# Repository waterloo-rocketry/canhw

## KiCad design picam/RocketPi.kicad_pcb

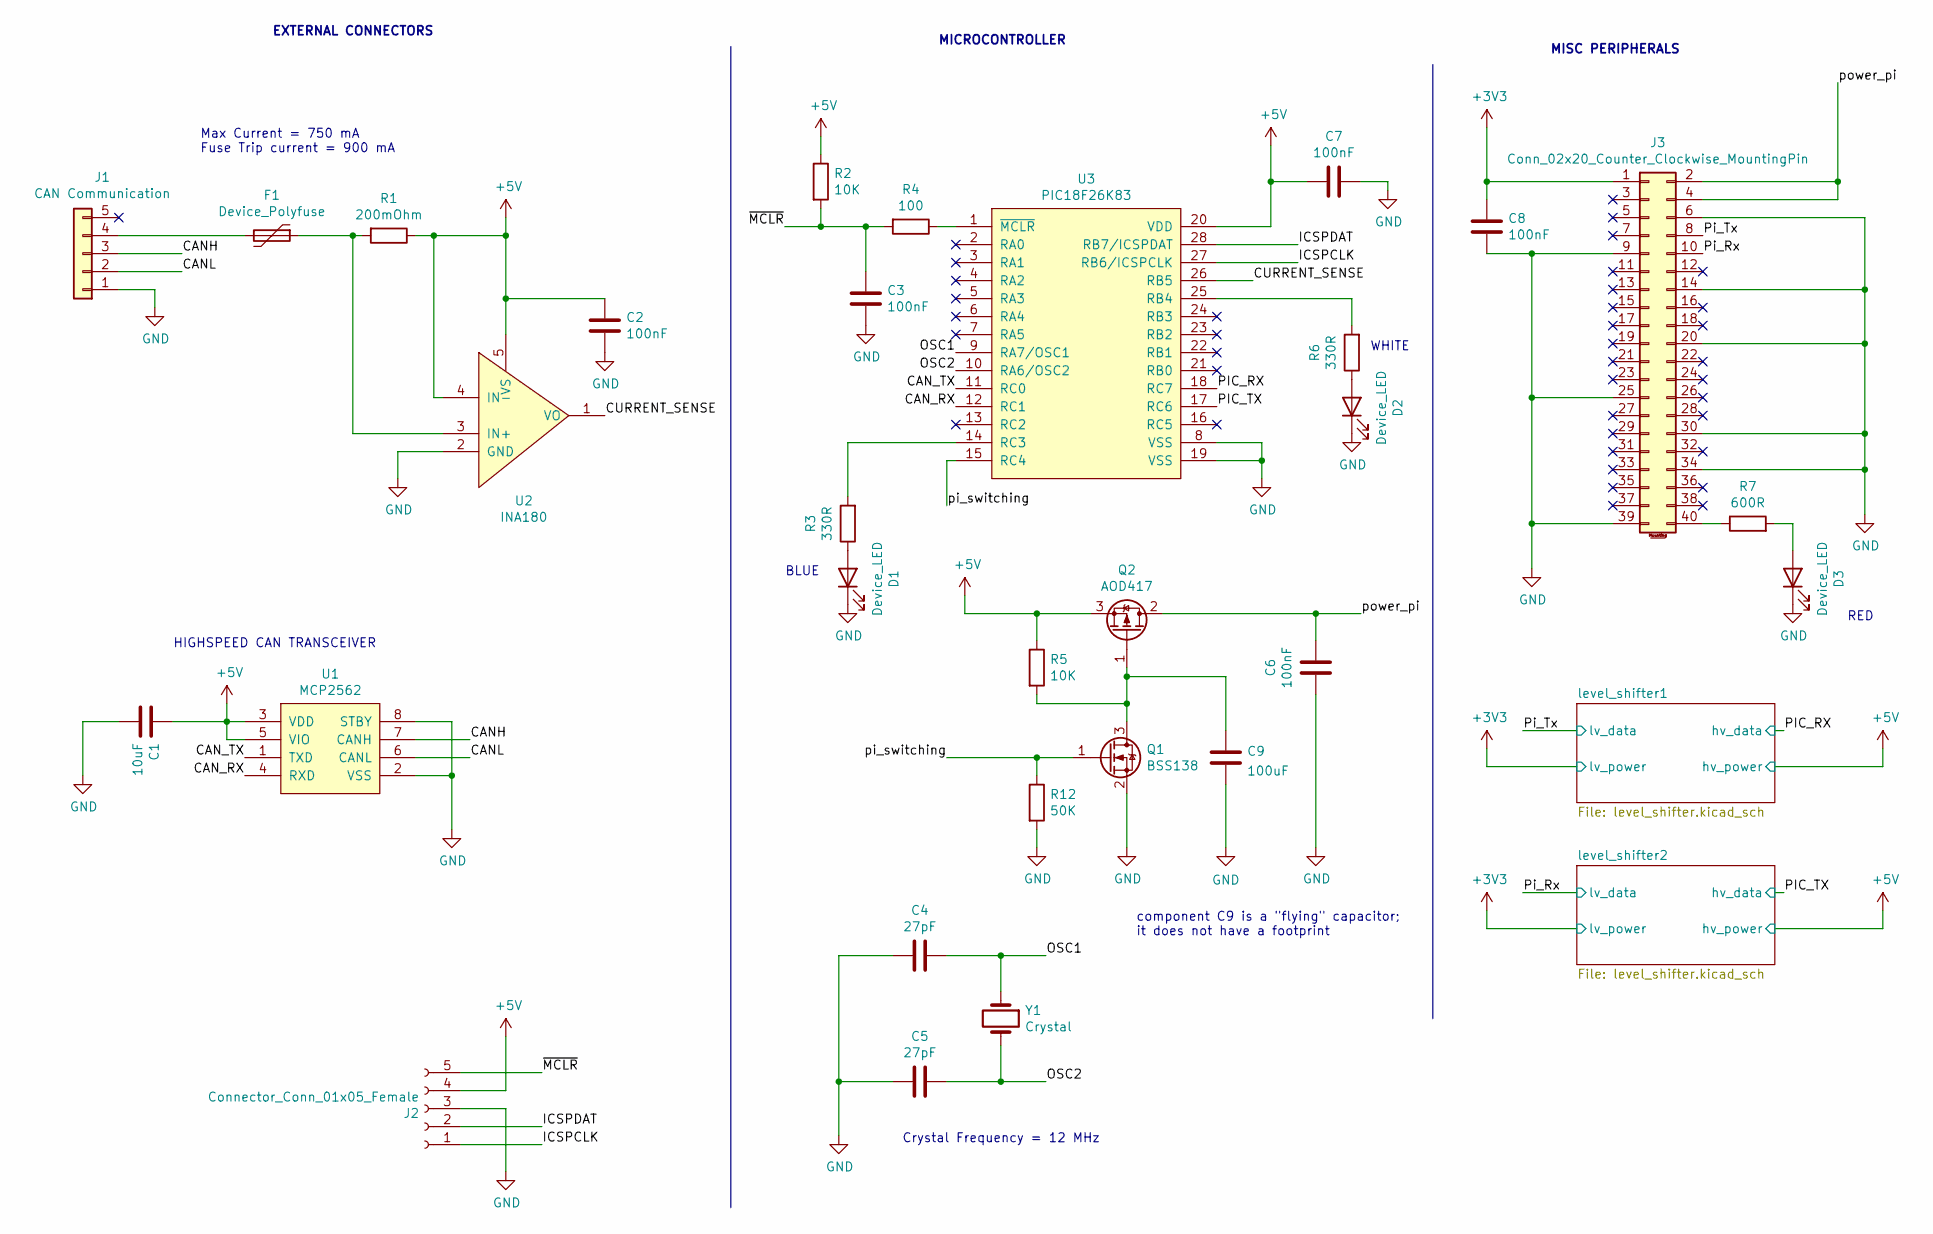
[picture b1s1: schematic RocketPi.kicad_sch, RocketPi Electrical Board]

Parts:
C1: 10uF; C_0805_2012Metric_Pad1.15x1.40mm_HandSolder
C2, C3, C6, C7, C8: 100nF; C_0805_2012Metric_Pad1.15x1.40mm_HandSolder
C4, C5: 27pF; C_0805_2012Metric_Pad1.15x1.40mm_HandSolder
C9: 100uF
D1, D2, D3: Device_LED; LED_0805_2012Metric_Pad1.15x1.40mm_HandSolder
F1: Device_Polyfuse; Fuse_0805_2012Metric_Pad1.15x1.40mm_HandSolder
J1: CAN Communication; connector_Harwin_M80-5000642
J2: Connector_Conn_01x05_Female; PinHeader_5x2.54_SMD_90deg_952-3198-1-ND
J3: Conn_02x20_Counter_Clockwise_MountingPin; PinHeader_2x20_P2.54mm_Vertical
Q1: BSS138; SOT-23
Q2: AOD417; TO-252-2
R1: 200mOhm; R_0805_2012Metric_Pad1.15x1.40mm_HandSolder
R2, R5: 10K; R_0805_2012Metric_Pad1.15x1.40mm_HandSolder
R3, R6: 330R; R_0805_2012Metric_Pad1.15x1.40mm_HandSolder
R4: 100; R_0805_2012Metric_Pad1.15x1.40mm_HandSolder
R7: 600R; R_0805_2012Metric_Pad1.15x1.40mm_HandSolder
R12: 50K; R_0805_2012Metric_Pad1.15x1.40mm_HandSolder
U1: MCP2562; SOIC-8_3.9x4.9mm_P1.27mm
U2: INA180; SOT-23-5_HandSoldering
U3: PIC18F26K83; SOIC-28W_7.5x17.9mm_P1.27mm
Y1: Crystal; Crystal_HC49-U_Vertical

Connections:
+3V3: C8.1, J3.1; also elsewhere on the board
+5V: C1.1, C2.1, C7.2, J2.4, Q2.3 (S), R1.1, R2.1, R5.1, U1.3 (VDD), U1.5 (VIO), U2.4 (IN-), U2.5 (VS), U3.20 (VDD); also elsewhere on the board
/CANH: J1.3, U1.7 (CANH)
/CANL: J1.2, U1.6 (CANL)
/CAN_RX: U1.4 (RXD), U3.12 (RC1)
/CAN_TX: U1.1 (TXD), U3.11 (RC0)
/CURRENT_SENSE: U2.1 (VO), U3.26 (RB5)
/ICSPCLK: J2.1, U3.27 (RB6/ICSPCLK)
/ICSPDAT: J2.2, U3.28 (RB7/ICSPDAT)
/OSC1: C4.1, U3.9 (RA7/OSC1), Y1.1
/OSC2: C5.1, U3.10 (RA6/OSC2), Y1.2
/PIC_RX: U3.18 (RC7); also elsewhere on the board
/PIC_TX: U3.17 (RC6); also elsewhere on the board
/Pi_Rx: J3.10; also elsewhere on the board
/Pi_Tx: J3.8; also elsewhere on the board
/pi_switching: Q1.1 (G), R12.1, U3.15 (RC4)
/power_pi: C6.1, J3.2, J3.4, Q2.2 (D)
/~MCLR: C3.1, J2.5, R2.2, R4.2
GND: C1.2, C2.2, C3.2, C4.2, C5.2, C6.2, C7.1, C8.2, C9.2, D1.1 (K), D2.1 (K), D3.1 (K), J1.1, J2.3, J3.6, J3.9, J3.14, J3.20, J3.25, J3.30, J3.34, J3.39, Q1.2 (S), R12.2, U1.2 (VSS), U1.8 (STBY), U2.2 (GND), U3.8 (VSS), U3.19 (VSS)
unnamed: D1.2 (A), R3.1
unnamed: D2.2 (A), R6.1
unnamed: D3.2 (A), R7.2
unnamed: F1.1, R1.2, U2.3 (IN+)
unnamed: F1.2, J1.4
unnamed: J3.40, R7.1
unnamed: C9.1, Q1.3 (D), Q2.1 (G), R5.2
unnamed: R3.2, U3.14 (RC3)
unnamed: R4.1, U3.1 (~MCLR)
unnamed: R6.2, U3.25 (RB4)

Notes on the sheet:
component C9 is a "flying" capacitor; it does not have a footprint
BLUE
WHITE
Max Current = 750 mA Fuse Trip current = 900 mA
MISC PERIPHERALS
MICROCONTROLLER
RED
HIGHSPEED CAN TRANSCEIVER
EXTERNAL CONNECTORS
Crystal Frequency = 12 MHz

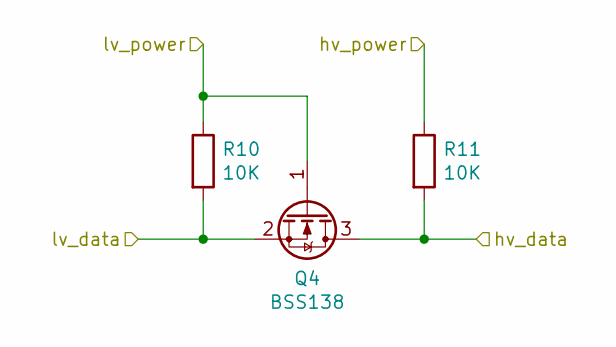
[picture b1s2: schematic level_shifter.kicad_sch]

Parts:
Q4: BSS138; SOT-23
R10, R11: 10K; R_0805_2012Metric_Pad1.15x1.40mm_HandSolder

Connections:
+3V3: Q4.1 (G), R10.1; also elsewhere on the board
+5V: R11.1; also elsewhere on the board
/PIC_TX: Q4.3 (D), R11.2; also elsewhere on the board
/Pi_Rx: Q4.2 (S), R10.2; also elsewhere on the board

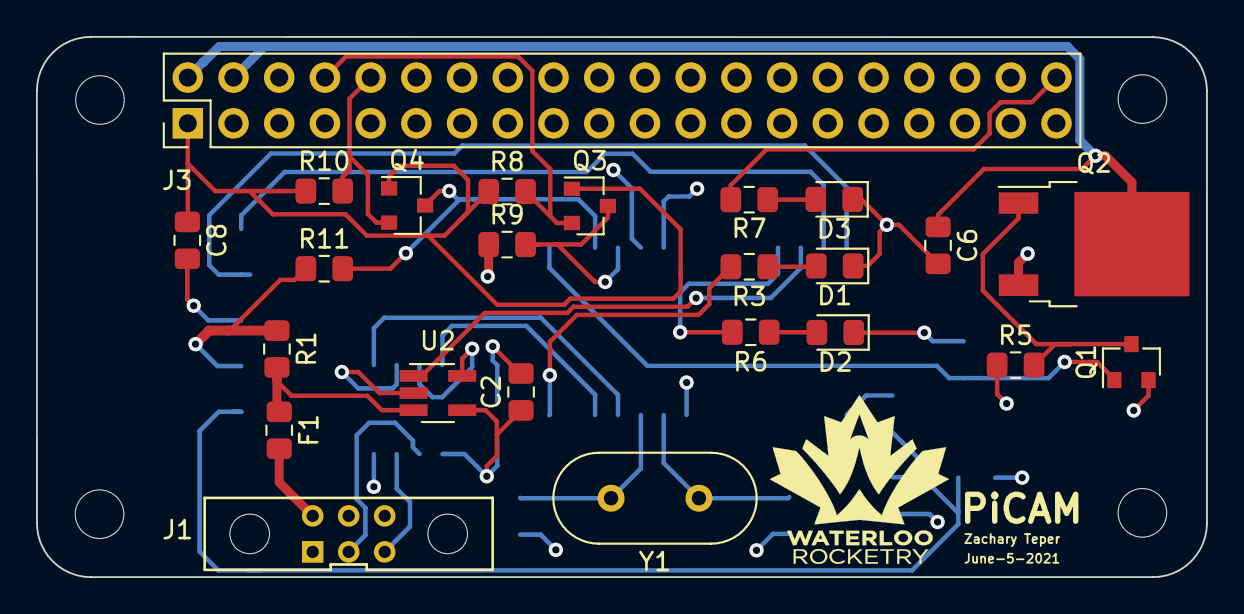
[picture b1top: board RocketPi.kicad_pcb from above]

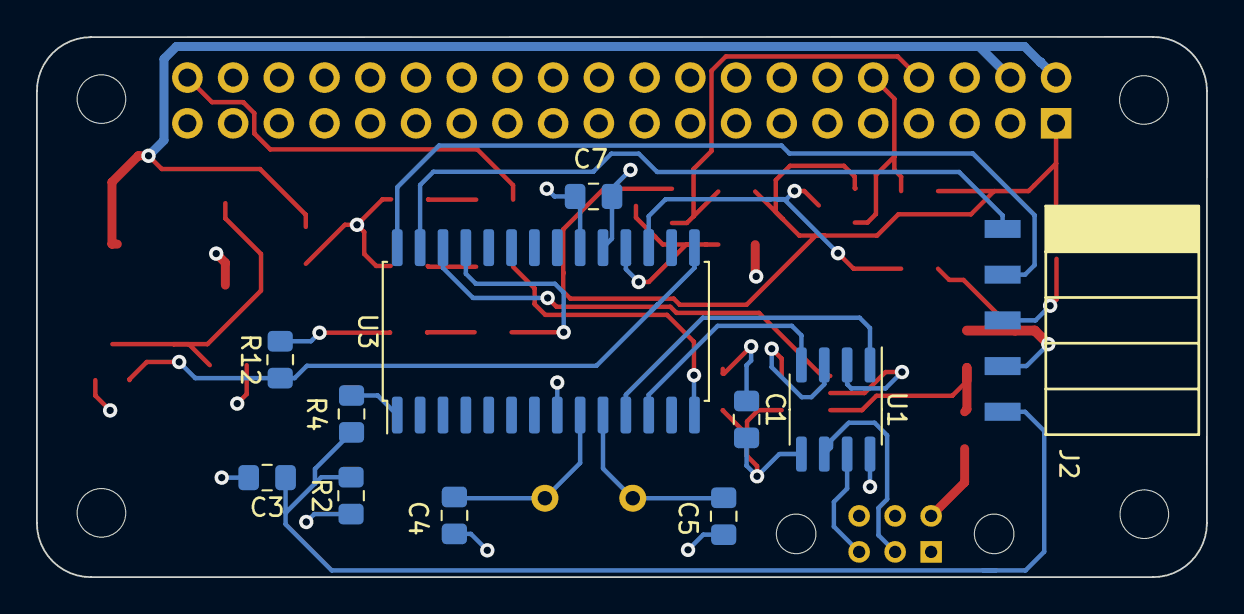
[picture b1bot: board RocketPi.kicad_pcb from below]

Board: 4 copper layers, 65.0 x 30.0 mm, 39 parts (11 on the bottom side), 29 nets.

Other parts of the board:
M1, M2, M3, M4: MountingHole_2.7mm
Q3: BSS138; SOT-23
R8, R9: 10K; R_0805_2012Metric_Pad1.15x1.40mm_HandSolder

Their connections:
+3V3: Q3.1, R8.1; also elsewhere on the board
+5V: R9.1; also elsewhere on the board
/PIC_RX: Q3.3, R9.2; also elsewhere on the board
/Pi_Tx: Q3.2, R8.2; also elsewhere on the board

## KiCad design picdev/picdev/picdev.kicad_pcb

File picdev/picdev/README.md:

This is a development board meant to be used for writing firmware for the CAN bus project while the main rocket boards are still in the hardware design phase. The board contains a PIC18F26K83 (which will be used on most subsystem boards inside the rocket) and a PIC16F1455 (which is used on the USB debug board). The PIC16F is connected to an external CAN module, allowing the two PICs to communicate with each other over CAN. 

The board is nicknamed "Keto" because it was borne out of a dislike of breadboards.

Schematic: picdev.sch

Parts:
C1, C2: 10uF; CP_Radial_D5.0mm_P2.50mm
F1: Fuse_Small; Fuse_1206_3216Metric_Pad1.24x1.80mm_HandSolder
J1: Power Conn; Pin_Header_Straight_1x02_Pitch2.54mm
J4: CAN Breakout; Pin_Header_Straight_1x02_Pitch2.54mm
JP1, JP2: Jumper_NC_Small; Pin_Header_Straight_1x02_Pitch2.54mm
R1: 120R; R_0805_HandSoldering
TP1, TP2: TestPoint; TestPoint_THTPad_D2.0mm_Drill1.0mm
U1: R-78E5.0-0.5; SIP3_11.6x8.5mm

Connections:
+5V: C2.1, U1.3; also elsewhere on the board
/PIC16F1455/CANH: J4.2, JP1.1; also elsewhere on the board
/PIC16F1455/CANL: J4.1, JP2.1; also elsewhere on the board
/PIC18F26K83/CANH: JP1.2, R1.1, TP1.1; also elsewhere on the board
/PIC18F26K83/CANL: JP2.2, R1.2, TP2.1; also elsewhere on the board
GND: C1.2, C2.2, J1.1, U1.2; also elsewhere on the board
unnamed: C1.1, F1.2, U1.1
unnamed: F1.1, J1.2

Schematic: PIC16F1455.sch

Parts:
C3, C5, C6: 0.1uF; C_0805_HandSoldering
C4: 10uF; CP_Radial_D5.0mm_P2.50mm
D1, D2: LED; LED_1206_3216Metric
J2: Programming Header; Pin_Header_Straight_1x05_Pitch2.54mm
J5: USB_B; USB_B_Horizontal
R2, R3: 10K; R_0805_HandSoldering
R4, R5: 330R; R_0805_HandSoldering
R12: 0; R_0805_HandSoldering
TP3, TP4: TestPoint; TestPoint_THTPad_D2.0mm_Drill1.0mm
U2: MCP2562; DIP-8_W7.62mm
U3: PIC16F1455; DIP-14_W7.62mm
U4: MCP2515; DIP-18_W7.62mm

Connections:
+5V: C4.1, C5.1, C6.1, D1.2, D2.2, J2.4, R2.1, R3.1, R12.1, U2.3 (VDD), U2.5 (VIO), U3.1 (VDD), U4.17 (~RESET), U4.18 (VDD); also elsewhere on the board
/PIC16F1455/CANH: U2.7 (CANH); also elsewhere on the board
/PIC16F1455/CANL: U2.6 (CANL); also elsewhere on the board
/PIC16F1455/CAN_INT: R3.2, U3.2 (RA5), U4.12 (~INT)
/PIC16F1455/CLKOUT: U3.3 (RA4), U4.8 (OSC1)
/PIC16F1455/CS: U3.7 (RC3), U4.16 (~CS)
/PIC16F1455/ICSPCLK: J2.1, U3.9 (RC1/ICSPCLK), U4.15 (SO)
/PIC16F1455/ICSPDAT: J2.2, U3.10 (RC0/ICSPDAT), U4.13 (SCK)
/PIC16F1455/MOSI: U3.8 (RC2), U4.14 (SI)
/PIC16F1455/USB_D+: J5.3 (D+), U3.13 (RA0/D+)
/PIC16F1455/USB_D-: J5.2 (D-), U3.12 (RA1/D-)
/PIC16F1455/~MCLR: J2.5, R2.2, U3.4 (RA3/~MCLR)
GND: C3.2, C4.2, C5.2, C6.2, J2.3, J5.4 (GND), J5.5 (Shield), U2.2 (VSS), U2.8 (STBY), U3.14 (VSS), U4.9 (VSS); also elsewhere on the board
unnamed: C3.1, U3.11 (VUSB3V3)
unnamed: D1.1, R4.1
unnamed: D2.1, R5.1
unnamed: J5.1 (VBUS), R12.2
unnamed: R4.2, U3.6 (RC4)
unnamed: R5.2, U3.5 (RC5)
unnamed: TP3.1, U2.1 (TXD), U4.1 (TXCAN)
unnamed: TP4.1, U2.4 (RXD), U4.2 (RXCAN)

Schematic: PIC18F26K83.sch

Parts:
C7: 0.1uF; C_0805_HandSoldering
C8: 10uF; CP_Radial_D5.0mm_P2.50mm
C9, C10: 26pF; C_0805_HandSoldering
D3, D4, D5, D6, D7: LED; LED_1206_3216Metric
J3: Programming Header; Pin_Header_Straight_1x05_Pitch2.54mm
J6: Conn_01x04_Female; Pin_Header_Straight_1x04_Pitch2.54mm
R6: 1OK; R_0805_HandSoldering
R7, R8, R9, R10, R11: 330R; R_0805_HandSoldering
TP5, TP6: TestPoint; TestPoint_THTPad_D2.0mm_Drill1.0mm
U5: MCP2562; DIP-8_W7.62mm
U6: PIC18F26K83; DIP-28_W7.62mm
Y1: Crystal; Crystal_HC49-4H_Vertical

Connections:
+5V: C7.2, C8.1, D3.2, D4.2, D5.2, D6.2, D7.2, J3.4, R6.1, U5.3 (VDD), U5.5 (VIO), U6.20; also elsewhere on the board
/PIC18F26K83/CANH: U5.7 (CANH); also elsewhere on the board
/PIC18F26K83/CANL: U5.6 (CANL); also elsewhere on the board
/PIC18F26K83/CAN_RX: TP6.1, U5.4 (RXD), U6.12
/PIC18F26K83/CAN_TX: TP5.1, U5.1 (TXD), U6.11
/PIC18F26K83/ICSPCLK: J3.1, U6.27
/PIC18F26K83/ICSPDAT: J3.2, U6.28
/PIC18F26K83/OSC1: C9.1, U6.9, Y1.1
/PIC18F26K83/OSC2: C10.1, U6.10, Y1.2
/PIC18F26K83/~MCLR: J3.5, R6.2, U6.1
GND: C7.1, C8.2, C9.2, C10.2, J3.3, U5.2 (VSS), U5.8 (STBY), U6.8, U6.19; also elsewhere on the board
unnamed: D3.1, R7.1
unnamed: D4.1, R8.1
unnamed: D5.1, R9.1
unnamed: D6.1, R10.1
unnamed: D7.1, R11.1
unnamed: J6.1, U6.2
unnamed: J6.2, U6.3
unnamed: J6.3, U6.4
unnamed: J6.4, U6.5
unnamed: R7.2, U6.25
unnamed: R8.2, U6.24
unnamed: R9.2, U6.23
unnamed: R10.2, U6.22
unnamed: R11.2, U6.21

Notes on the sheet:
completely unecessary

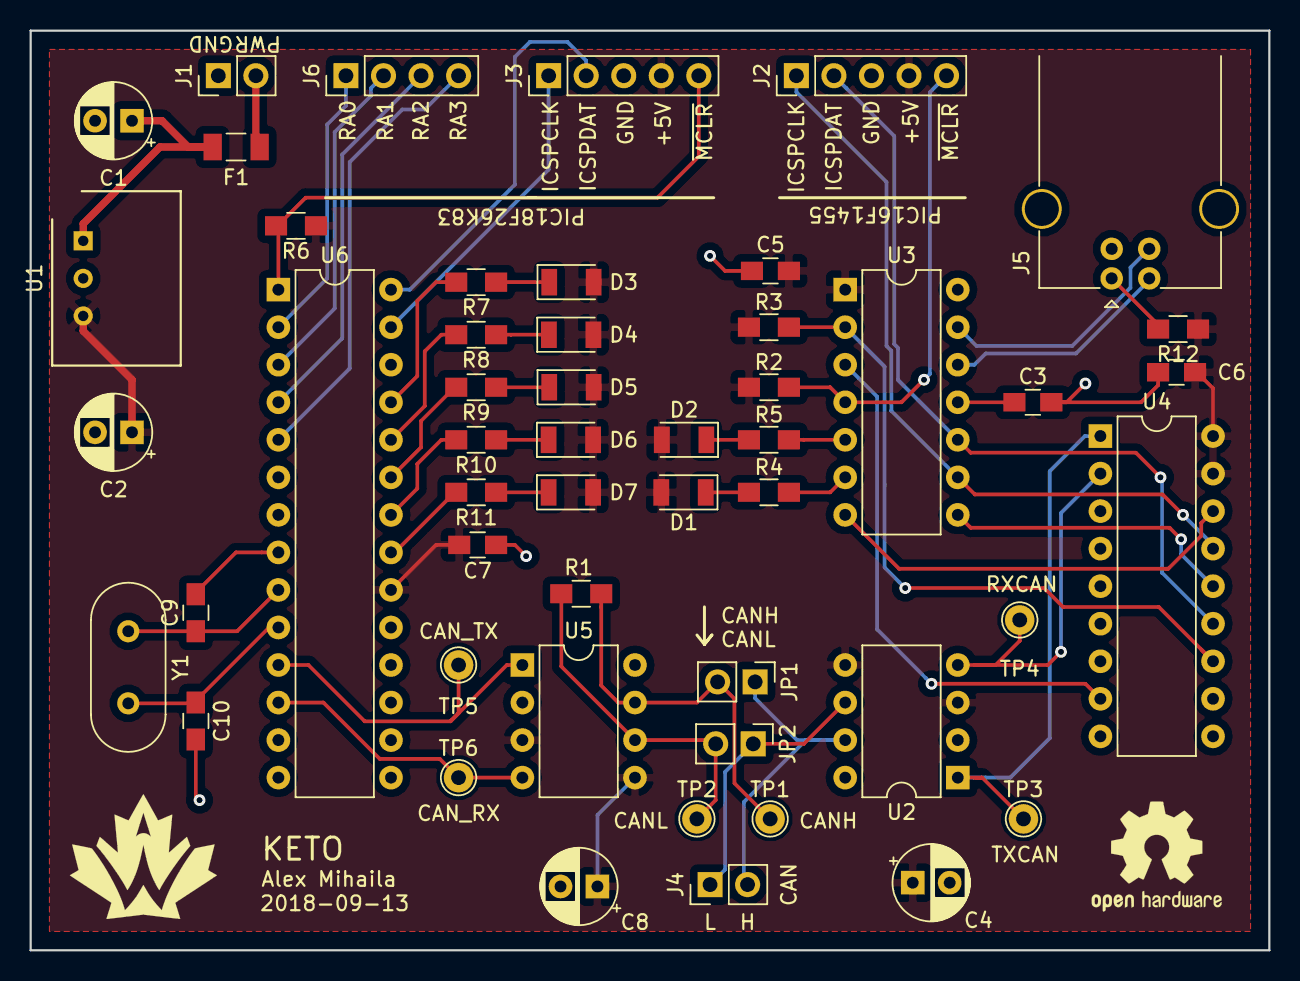
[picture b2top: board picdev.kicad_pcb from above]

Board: 2 copper layers, 83.8 x 62.2 mm, 51 parts (0 on the bottom side), 46 nets.

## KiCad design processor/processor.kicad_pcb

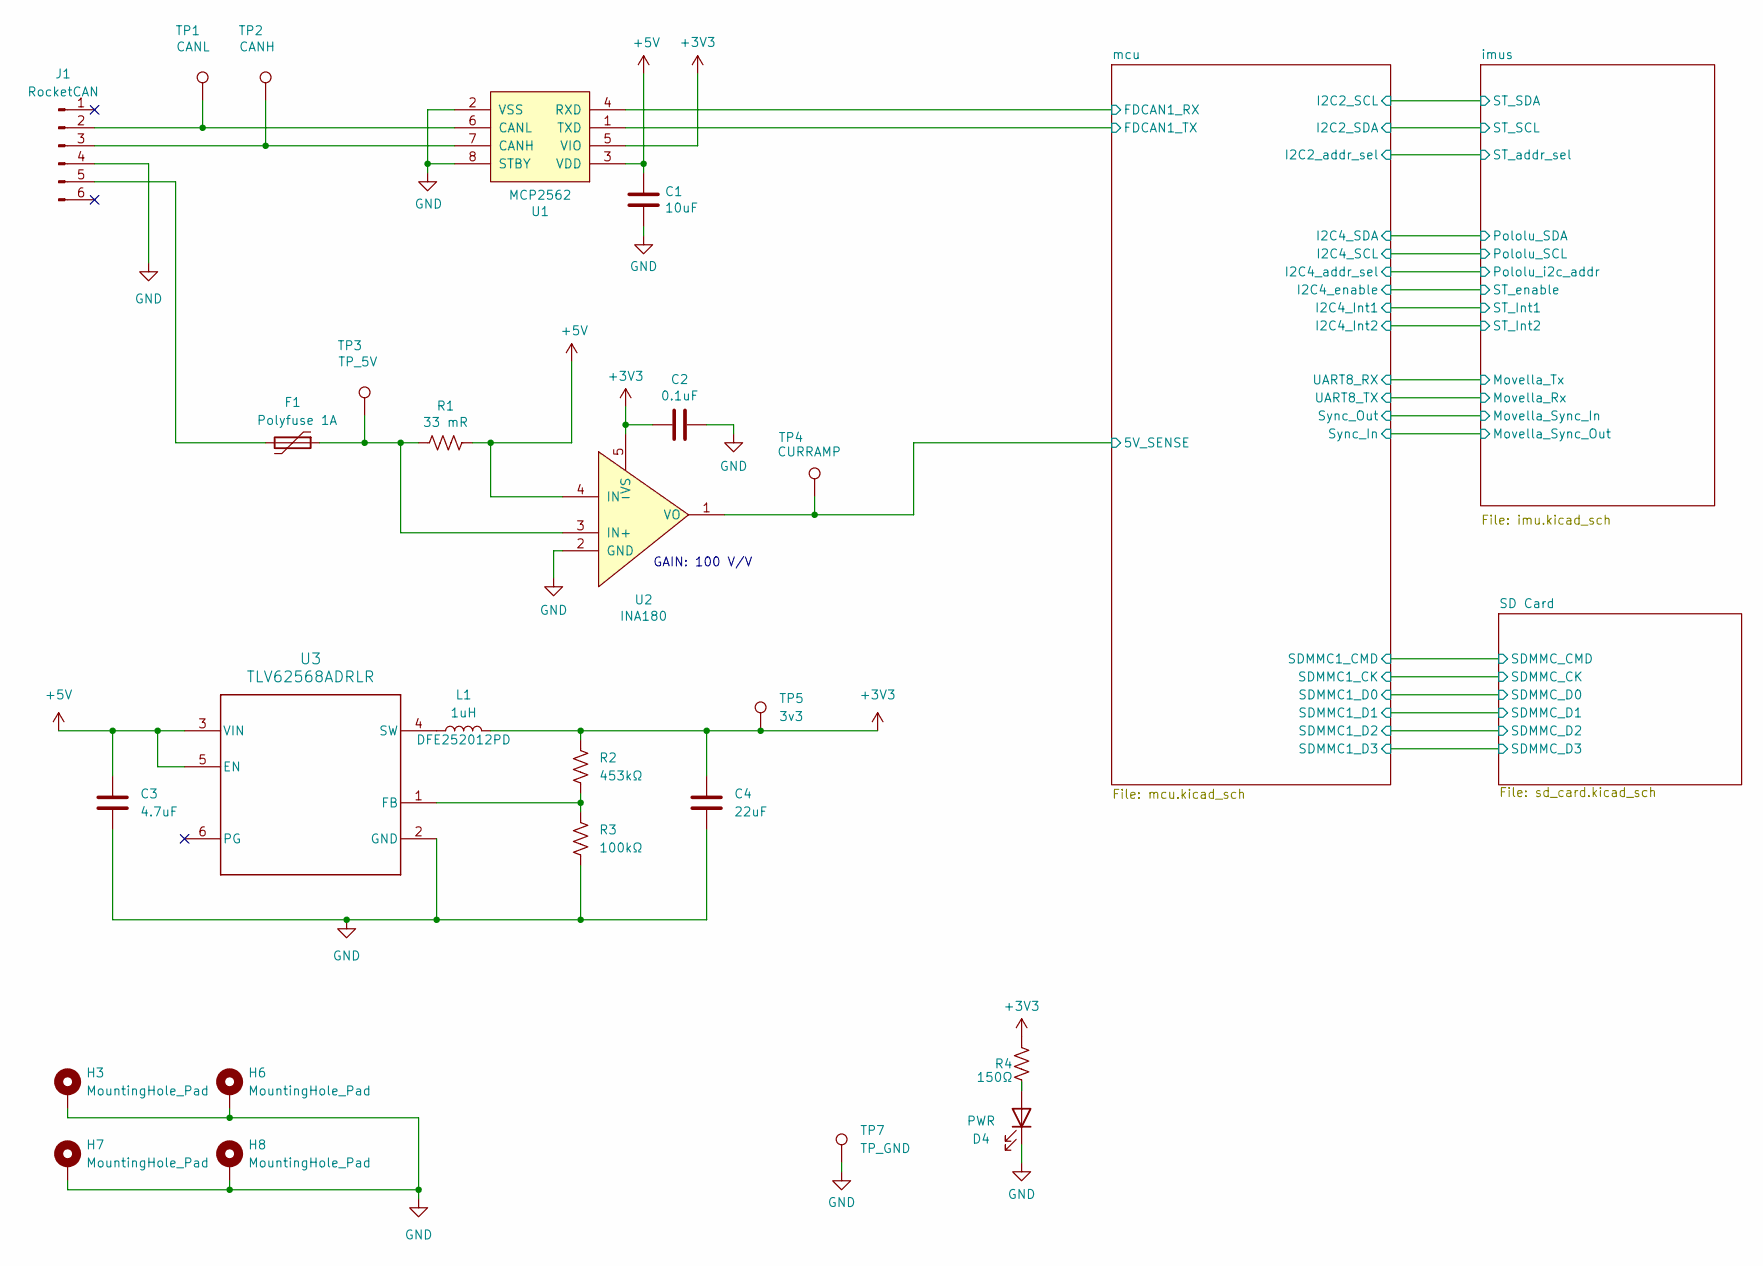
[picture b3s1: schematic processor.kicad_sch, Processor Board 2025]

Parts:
C1: 10uF; C_0805_2012Metric_Pad1.18x1.45mm_HandSolder; LCSC Part # C15850
C2: 0.1uF; C_0805_2012Metric_Pad1.18x1.45mm_HandSolder; LCSC Part # C49678
C3: 4.7uF; C_0805_2012Metric_Pad1.18x1.45mm_HandSolder; LCSC Part # C1779
C4: 22uF; C_0805_2012Metric_Pad1.18x1.45mm_HandSolder; LCSC Part # C45783
D4: PWR; LED_1206_3216Metric_Pad1.42x1.75mm_HandSolder; LCSC Part # C434441
F1: Polyfuse 1A; Fuse_1206_3216Metric_Pad1.42x1.75mm_HandSolder; LCSC Part # C20800
H3, H6, H7, H8: MountingHole_Pad; MountingHole_3.2mm_M3_DIN965_Pad
J1: RocketCAN; connector_Harwin_G125–MG10605M4P
L1: 1uH; IND_DFE252012PD-1R0M=P2_MUR; Part Number DFE252012PD; LCSC Part # C2917900
R1: 33 mR; R_1206_3216Metric_Pad1.30x1.75mm_HandSolder; LCSC Part # C912764
R2: 453kΩ; R_0805_2012Metric_Pad1.20x1.40mm_HandSolder; LCSC Part # C101739
R3: 100kΩ; R_0805_2012Metric_Pad1.20x1.40mm_HandSolder; LCSC Part # C149504
R4: 150Ω; R_0805_2012Metric_Pad1.20x1.40mm_HandSolder; LCSC Part # C17471
TP1: CANL; TestPoint_Pad_1.5x1.5mm
TP2: CANH; TestPoint_Pad_1.5x1.5mm
TP3: TP_5V; TestPoint_Keystone_5000-5004_Miniature
TP4: CURRAMP; TestPoint_Pad_1.5x1.5mm
TP5: 3v3; TestPoint_Keystone_5000-5004_Miniature
TP7: TP_GND; TestPoint_Keystone_5000-5004_Miniature
U1: MCP2562; SOIC-8_3.9x4.9mm_P1.27mm; LCSC Part # C191417
U2: INA180; SOT-23-5_HandSoldering; LCSC Part # C2059240
U3: TLV62568ADRLR; DRL0006A; LCSC Part # C398372

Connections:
+3V3: C2.2, C4.1, L1.2, R2.1, R4.1, TP5.1, U1.5 (VIO), U2.5 (VS); also elsewhere on the board
+5V: C1.1, C3.1, R1.1, U1.3 (VDD), U2.4 (IN-), U3.3 (VIN), U3.5 (EN); also elsewhere on the board
/mcu/5V_SENSE: TP4.1, U2.1 (VO); also elsewhere on the board
/mcu/FDCAN1_RX: U1.4 (RXD); also elsewhere on the board
/mcu/FDCAN1_TX: U1.1 (TXD); also elsewhere on the board
GND: C1.2, C2.1, C3.2, C4.2, D4.1 (K), H3.1, J1.4, R3.2, TP7.1, U1.2 (VSS), U1.8 (STBY), U2.2 (GND), U3.2 (GND); also elsewhere on the board
unnamed: D4.2 (A), R4.2
unnamed: J1.2, TP1.1, U1.6 (CANL)
unnamed: J1.3, TP2.1, U1.7 (CANH)
unnamed: F1.2, J1.5
unnamed: F1.1, R1.2, TP3.1, U2.3 (IN+)
unnamed: R2.2, R3.1, U3.1 (FB)
unnamed: L1.1, U3.4 (SW)

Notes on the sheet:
GAIN: 100 V/V

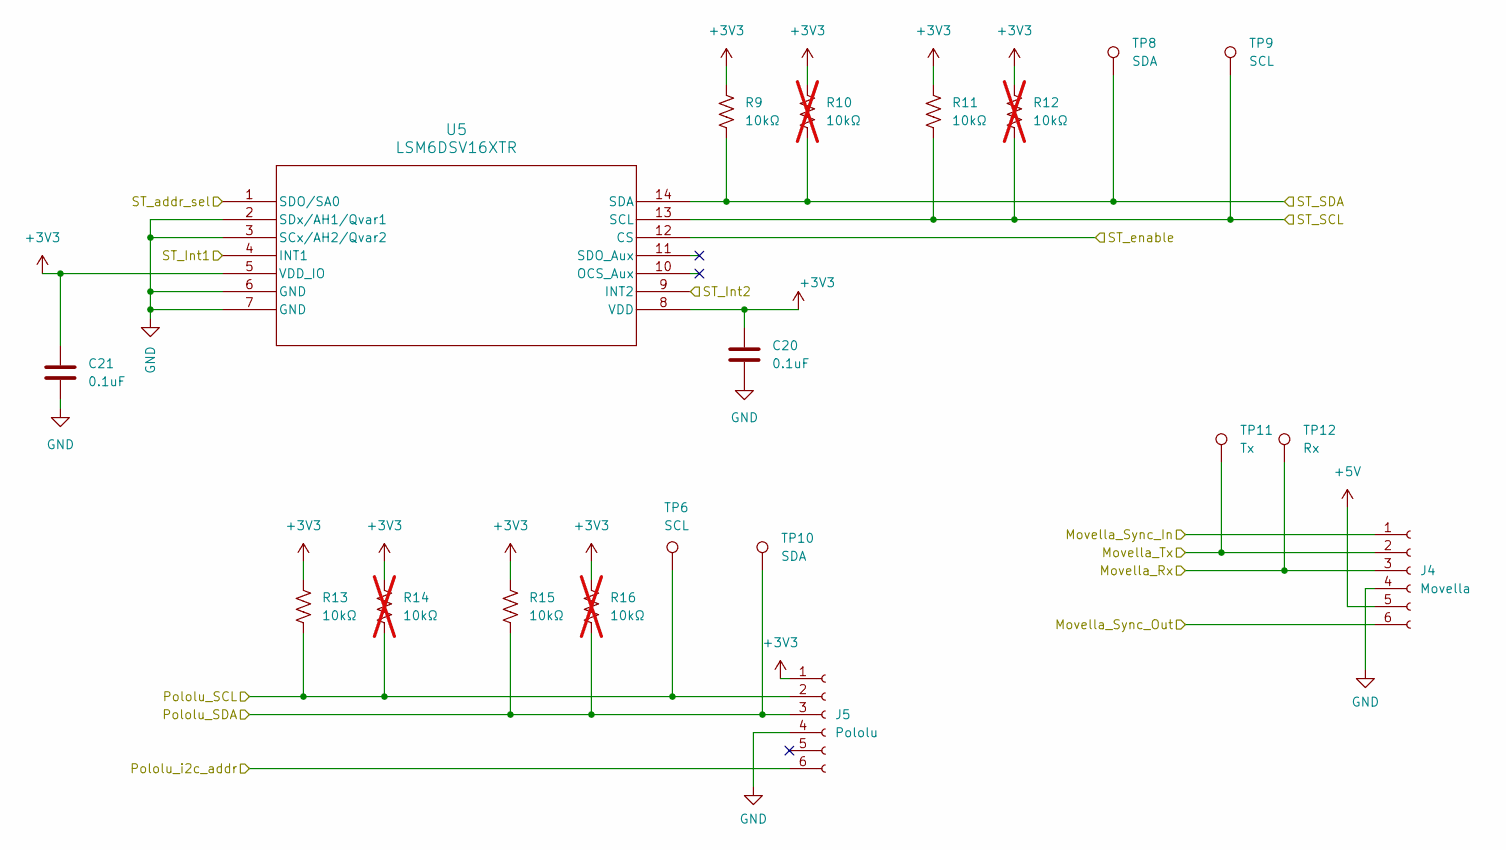
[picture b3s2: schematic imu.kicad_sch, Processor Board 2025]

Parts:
C20, C21: 0.1uF; C_0805_2012Metric_Pad1.18x1.45mm_HandSolder; LCSC Part # C49678
J4: Movella; connector_Harwin_G125–MG10605M4P
J5: Pololu; connector_Harwin_G125–MG10605M4P
R9, R11, R13, R15: 10kΩ; R_0805_2012Metric_Pad1.20x1.40mm_HandSolder; LCSC Part # C17414
R10, R12, R14, R16: 10kΩ; R_0805_2012Metric_Pad1.20x1.40mm_HandSolder; LCSC Part # C17414; not fitted
TP6: SCL; TestPoint_Keystone_5000-5004_Miniature
TP8: SDA; TestPoint_Pad_D1.5mm
TP9: SCL; TestPoint_Pad_D1.5mm
TP10: SDA; TestPoint_Keystone_5000-5004_Miniature
TP11: Tx; TestPoint_Keystone_5000-5004_Miniature
TP12: Rx; TestPoint_Keystone_5000-5004_Miniature
U5: LSM6DSV16XTR; LGA-14L_2p5X3p0X0p86_STM; LCSC Part # C5267406

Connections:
+3V3: C20.1, C21.1, J5.1, R9.1, R10.1, R11.1, R12.1, R13.1, R14.1, R15.1, R16.1, U5.5 (VDD_IO), U5.8 (VDD); also elsewhere on the board
+5V: J4.5; also elsewhere on the board
/imus/Movella_Rx: J4.3, TP12.1; also elsewhere on the board
/imus/Movella_Sync_In: J4.1; also elsewhere on the board
/imus/Movella_Sync_Out: J4.6; also elsewhere on the board
/imus/Movella_Tx: J4.2, TP11.1; also elsewhere on the board
/imus/Pololu_SCL: J5.2, R13.2, R14.2, TP6.1; also elsewhere on the board
/imus/Pololu_SDA: J5.3, R15.2, R16.2, TP10.1; also elsewhere on the board
/imus/Pololu_i2c_addr: J5.6; also elsewhere on the board
/imus/ST_Int1: U5.4 (INT1); also elsewhere on the board
/imus/ST_Int2: U5.9 (INT2); also elsewhere on the board
/imus/ST_SCL: R11.2, R12.2, TP9.1, U5.13 (SCL); also elsewhere on the board
/imus/ST_SDA: R9.2, R10.2, TP8.1, U5.14 (SDA); also elsewhere on the board
/imus/ST_addr_sel: U5.1 (SDO/SA0); also elsewhere on the board
/imus/ST_enable: U5.12 (CS); also elsewhere on the board
GND: C20.2, C21.2, J4.4, J5.4, U5.2 (SDx/AH1/Qvar1), U5.3 (SCx/AH2/Qvar2), U5.6 (GND), U5.7 (GND); also elsewhere on the board

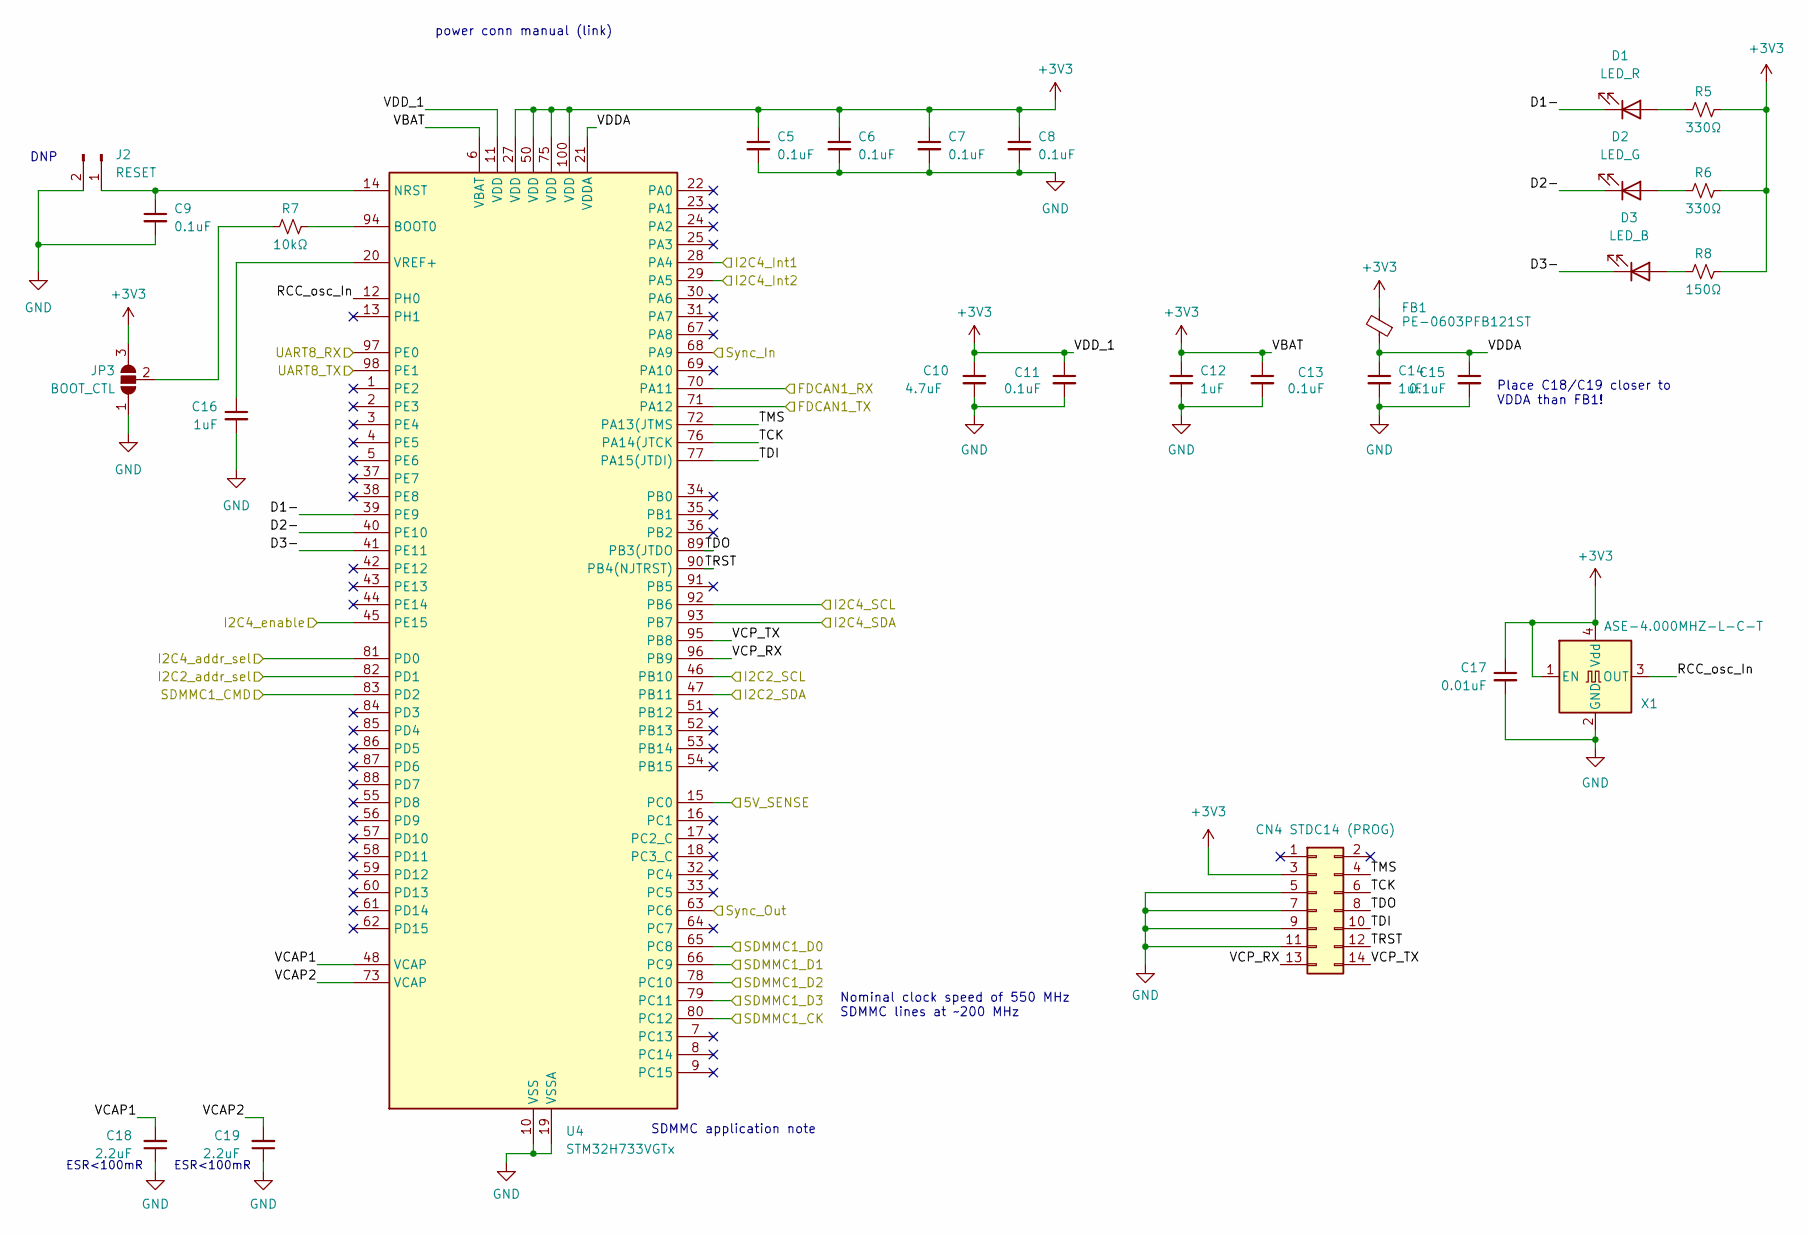
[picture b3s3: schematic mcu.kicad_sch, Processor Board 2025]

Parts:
C5, C6, C7, C8, C9, C11, C13, C15: 0.1uF; C_0805_2012Metric_Pad1.18x1.45mm_HandSolder; LCSC Part # C49678
C10: 4.7uF; C_0805_2012Metric_Pad1.18x1.45mm_HandSolder; LCSC Part # C1779
C12, C14, C16: 1uF; C_0805_2012Metric_Pad1.18x1.45mm_HandSolder; LCSC Part # C28323
C17: 0.01uF; C_0805_2012Metric_Pad1.18x1.45mm_HandSolder; LCSC Part # C1710
C18, C19: 2.2uF; C_0805_2012Metric_Pad1.18x1.45mm_HandSolder; LCSC Part # C377773
D1: LED_R; LED_1206_3216Metric_Pad1.42x1.75mm_HandSolder; LCSC Part # C7496845
D2: LED_G; LED_1206_3216Metric_Pad1.42x1.75mm_HandSolder; LCSC Part # C7496843
D3: LED_B; LED_1206_3216Metric_Pad1.42x1.75mm_HandSolder; LCSC Part # C434440
FB1: PE-0603PFB121ST; C_0603_1608Metric_Pad1.08x0.95mm_HandSolder; LCSC Part # C139186
J2: RESET; PinHeader_1x02_P1.00mm_Vertical
J3: CN4 STDC14 (PROG); PinSocket_2x07_P1.27mm_Vertical_SMD; DigiKey Part # 609-20021321-00014C1LFTR-ND
JP3: BOOT_CTL; SolderJumper-3_P1.3mm_Open_Pad1.0x1.5mm_NumberLabels
R5, R6: 330Ω; R_0805_2012Metric_Pad1.20x1.40mm_HandSolder; LCSC Part # C17630
R7: 10kΩ; R_0805_2012Metric_Pad1.20x1.40mm_HandSolder; LCSC Part # C17414
R8: 150Ω; R_0805_2012Metric_Pad1.20x1.40mm_HandSolder; LCSC Part # C17471
U4: STM32H733VGTx; LQFP-100_14x14mm_P0.5mm; LCSC Part # C730160
X1: ASE-4.000MHZ-L-C-T; Oscillator_SMD_Abracon_ASE-4Pin_3.2x2.5mm; LCSC Part # C437121

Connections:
+3V3: C5.1, C6.1, C7.1, C8.1, C10.1, C11.1, C12.1, C13.1, C17.1, FB1.2, J3.3, JP3.3 (B), R5.1, R6.1, R8.1, U4.6 (VBAT), U4.11 (VDD), U4.27 (VDD), U4.50 (VDD), U4.75 (VDD), U4.100 (VDD), X1.1 (EN), X1.4 (Vdd); also elsewhere on the board
/SD Card/SDMMC_CK: U4.80 (PC12); also elsewhere on the board
/SD Card/SDMMC_CMD: U4.83 (PD2); also elsewhere on the board
/SD Card/SDMMC_D0: U4.65 (PC8); also elsewhere on the board
/SD Card/SDMMC_D1: U4.66 (PC9); also elsewhere on the board
/SD Card/SDMMC_D2: U4.78 (PC10); also elsewhere on the board
/SD Card/SDMMC_D3: U4.79 (PC11); also elsewhere on the board
/imus/Movella_Rx: U4.98 (PE1); also elsewhere on the board
/imus/Movella_Sync_In: U4.63 (PC6); also elsewhere on the board
/imus/Movella_Sync_Out: U4.68 (PA9); also elsewhere on the board
/imus/Movella_Tx: U4.97 (PE0); also elsewhere on the board
/imus/Pololu_SCL: U4.92 (PB6); also elsewhere on the board
/imus/Pololu_SDA: U4.93 (PB7); also elsewhere on the board
/imus/Pololu_i2c_addr: U4.81 (PD0); also elsewhere on the board
/imus/ST_Int1: U4.28 (PA4); also elsewhere on the board
/imus/ST_Int2: U4.29 (PA5); also elsewhere on the board
/imus/ST_SCL: U4.47 (PB11); also elsewhere on the board
/imus/ST_SDA: U4.46 (PB10); also elsewhere on the board
/imus/ST_addr_sel: U4.82 (PD1); also elsewhere on the board
/imus/ST_enable: U4.45 (PE15); also elsewhere on the board
/mcu/5V_SENSE: U4.15 (PC0); also elsewhere on the board
/mcu/D1-: D1.1 (K), U4.39 (PE9)
/mcu/D2-: D2.1 (K), U4.40 (PE10)
/mcu/D3-: D3.1 (K), U4.41 (PE11)
/mcu/FDCAN1_RX: U4.70 (PA11); also elsewhere on the board
/mcu/FDCAN1_TX: U4.71 (PA12); also elsewhere on the board
/mcu/RCC_osc_In: U4.12 (PH0), X1.3 (OUT)
/mcu/TCK: J3.6, U4.76 (PA14(JTCK)
/mcu/TDI: J3.10, U4.77 (PA15(JTDI))
/mcu/TDO: J3.8, U4.89 (PB3(JTDO)
/mcu/TMS: J3.4, U4.72 (PA13(JTMS)
/mcu/TRST: J3.12, U4.90 (PB4(NJTRST))
/mcu/VCAP1: C18.2, U4.48 (VCAP)
/mcu/VCAP2: C19.2, U4.73 (VCAP)
/mcu/VCP_RX: J3.13, U4.96 (PB9)
/mcu/VCP_TX: J3.14, U4.95 (PB8)
/mcu/VDDA: C14.1, C15.1, FB1.1, U4.21 (VDDA)
GND: C5.2, C6.2, C7.2, C8.2, C9.2, C10.2, C11.2, C12.2, C13.2, C14.2, C15.2, C16.2, C17.2, C18.1, C19.1, J2.2, J3.5, J3.7, J3.9, J3.11, JP3.1 (A), U4.10 (VSS), U4.19 (VSSA), U4.26 (VSS), U4.49 (VSS), U4.74 (VSS), U4.99 (VSS), X1.2 (GND); also elsewhere on the board
unnamed: D1.2 (A), R5.2
unnamed: D2.2 (A), R6.2
unnamed: D3.2 (A), R8.2
unnamed: C9.1, J2.1, U4.14 (NRST)
unnamed: JP3.2 (C), R7.2
unnamed: R7.1, U4.94 (BOOT0)
unnamed: C16.1, U4.20 (VREF+)

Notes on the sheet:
ESR<100mR
Nominal clock speed of 550 MHz SDMMC lines at ~200 MHz
DNP
power conn manual (link)
Place C18/C19 closer to VDDA than FB1!
SDMMC application note

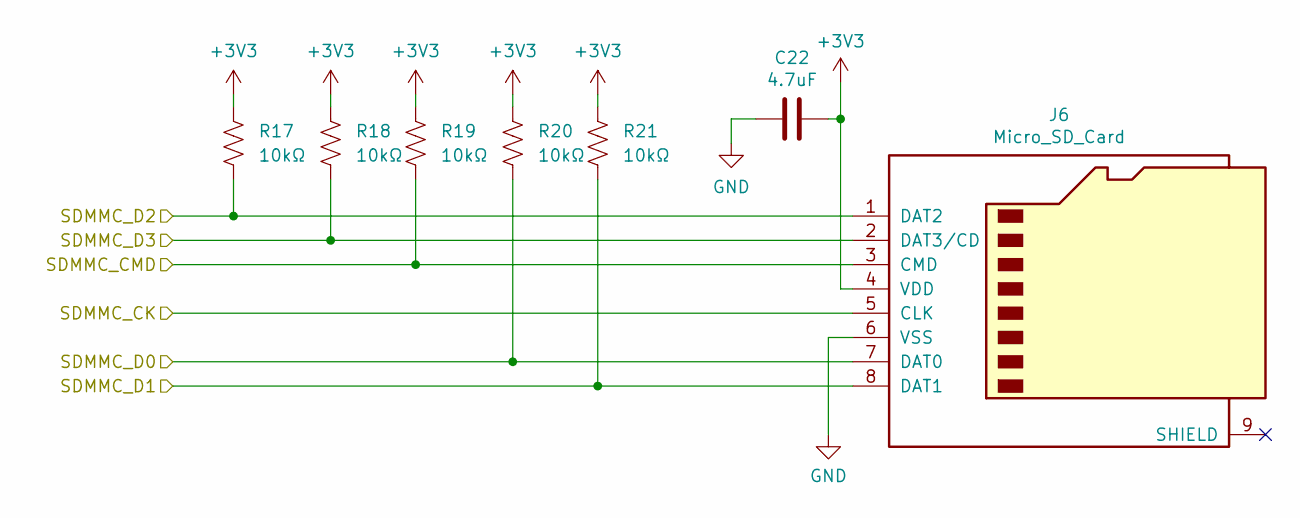
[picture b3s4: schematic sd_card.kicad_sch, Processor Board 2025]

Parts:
C22: 4.7uF; C_0805_2012Metric_Pad1.18x1.45mm_HandSolder; LCSC Part # C1779
J6: Micro_SD_Card; microSD_Molex_WM6698CT-ND; DigiKey Part # WM6698TR-ND
R17, R18, R19, R20, R21: 10kΩ; R_0805_2012Metric_Pad1.20x1.40mm_HandSolder; LCSC Part # C17414

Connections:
+3V3: C22.1, J6.4 (VDD), R17.1, R18.1, R19.1, R20.1, R21.1; also elsewhere on the board
/SD Card/SDMMC_CK: J6.5 (CLK); also elsewhere on the board
/SD Card/SDMMC_CMD: J6.3 (CMD), R19.2; also elsewhere on the board
/SD Card/SDMMC_D0: J6.7 (DAT0), R20.2; also elsewhere on the board
/SD Card/SDMMC_D1: J6.8 (DAT1), R21.2; also elsewhere on the board
/SD Card/SDMMC_D2: J6.1 (DAT2), R17.2; also elsewhere on the board
/SD Card/SDMMC_D3: J6.2 (DAT3/CD), R18.2; also elsewhere on the board
GND: C22.2, J6.6 (VSS); also elsewhere on the board
